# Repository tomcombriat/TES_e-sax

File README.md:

# TES - e-sax

More infos: https://t-e-s.frama.site/en/tesaxophone

The E-sax is an EWI made out of a real sax. It outputs MIDI signals that can be used to generate sounds using a synthesizer for instance the [10k synth](https://github.com/tomcombriat/TES_10-knobs-synth). It is design to provide saxophone players a digital instrument to which they can transition easily. Additionnaly from the "standard" behavior it also have features that are allowed by a digital instrument:

- EWI mode which tries to give a more ergonomic keying (E mode)
- chords (C mode)
- arpegiators (A and R modes)

## What is in this repo?
The [hardware](hardware/) folder contains the kicad project for the PCB used in the e-sax alongside with the Cu and Fab masks. It is single sided in order to make its construction possible for an hobbyist. Note that the isolations and the routes are fairly small (around 200 microns) so you will need to have a fairly optimized setup to be able to make this PCB correctly.

The [software](software/) folder contains the embedded program that is embedded in the chip. Note that it will need some configurations for any particular saxophone.

The main MCU is a cheap BluePill STM32, programmed using the [Arduino STM32 library](https://github.com/stm32duino/Arduino_Core_STM32) and a FTDI.

## Making
This gives some guidelines in order to allow people to make such an E-sax themselves. It precludes that the PCB is already printed and drilled.

Note: no 3D parts are included in this repo for now. Except for the beak, every part usually need to be redesigned for a different saxophone. Do not hesitate to contact me on that.

### Bill of Materials 

- 24 resistors 1-10k, noted R on the PCB
- 1 resistor 33
- 2 resistors 22k (optionnal)
- 1 resistor 10
- 1 BluePill
- 1 FTDI chip to program the BluePill
- 3 74HC165 Parallel-to-Serial shift registers
- enough header
- 1 SSD1306 Oled screen (*I2C*)
- 1 MPX5010 differential pressure sensor
- 1 joystick with a click
- a good amount of flexible thin wire (around 26 AWG, silicon cover)
- Dupond cables
- a good amount of copper tape
- 1 3-AA battery holder
- 1 MIDI female to solder
- 1 switch (non-momentary)
- 2 pairs (male and female) of JST connectors 3 pins
- 1 pair of JST connectors 5 pins
- 10 magnets (10x4x2mm^3) (optionnal)

### Wiring the saxophone

The controller needs to know what keys are pressed at any given time in order to be able to generate the correct MidiNote for a synthesizer. In order for the behavior to be as close as possible to a real saxophone, the sensors are positionned on the pads and not on the keys: if a key closing a pad is not pressed enough to close the pad the controller will consider it "open" just like it would be for a real saxophone. All the wires for the pads are going through the sax body.

The saxophone is a complex instrument and not every pad can be dismounted "alone": it is usual that some of them need other to be removed first in order to be dismounted.

#### Dismounting
This is why it is usually easier to dismount all the keys first and wire them on remounting.
Note: take some notes about which keys did you dismounted first: as the order matters they will need to be remounted in the _reverse order_. My personnal way of doing it is to write on every part a number and a letter (the latter only if this is a pad): the number denotes the order of dismounting (first dismounted part will be labelled "1", second "2"…) and the letter denotes the hole the pad is covering. I also write the same letter next to, or in, the hole which is covered by the pad. This way, upon remounting, one can start by the part with highest number, spot its hole (if any) and remount it.

#### Wiring the pads

The pads can be wired upon remounting. All pads need to be wired except the one which is just above the left hand forefinger which is not independant from the pad located under the left hand forefinger.

The sensor is composed of a thin copper layer glued to the pad and wire to the PCB. Using a push-up resistor, and by placing the whole sax body at GND the pad will behave as a switch:

- closed, the potential of the copper part will be at GND as it is in contact with the body
- open, the potential will be at 3.3V, thanks to a push-up resistor.

The copper tape needs to be glued to the pad:

- cut a piece of copper tape that matches more or less the dimension of the pad. The exact size of this piece is not critical but:
  - it need to cover some of the parts of the pad which are in contact with the body when closed. If possible at two different locations meaning that the length of this copper part should be at least be equal to the diameter of the hole covered by the pad.
  - it should not be too long either in order not to touch the metallic part of the key.
- apply a thin layer of neopren glue on the **tape** side of the copper, it should cover it all. Beware not to put some glue on the "clear" part of the copper
- apply a thin layer of neopren on the pad, it should match the dimensions of the piece of copper.
- wait from 10 to 15 minutes
- apply the copper, glue side of the tape facing the glue side of the pad, it should stick immediatly so the first attempt should be well positionned.
- using a soldering iron, add some solder at **the middle of the pad**, it should not touch the part where the pad touches the body.
- soldier a flexible wire long enough to go from the corresponding hole to the bell plus 5cm to it.
- put the wire in the hole and make it go to the bell throught the body (this can be hard for some keys) and tape it to the bell.
- remount the key on its hole.
- if done correctly, the key should action seemlessly and feel as natural as before.
- start again for all the other keys.

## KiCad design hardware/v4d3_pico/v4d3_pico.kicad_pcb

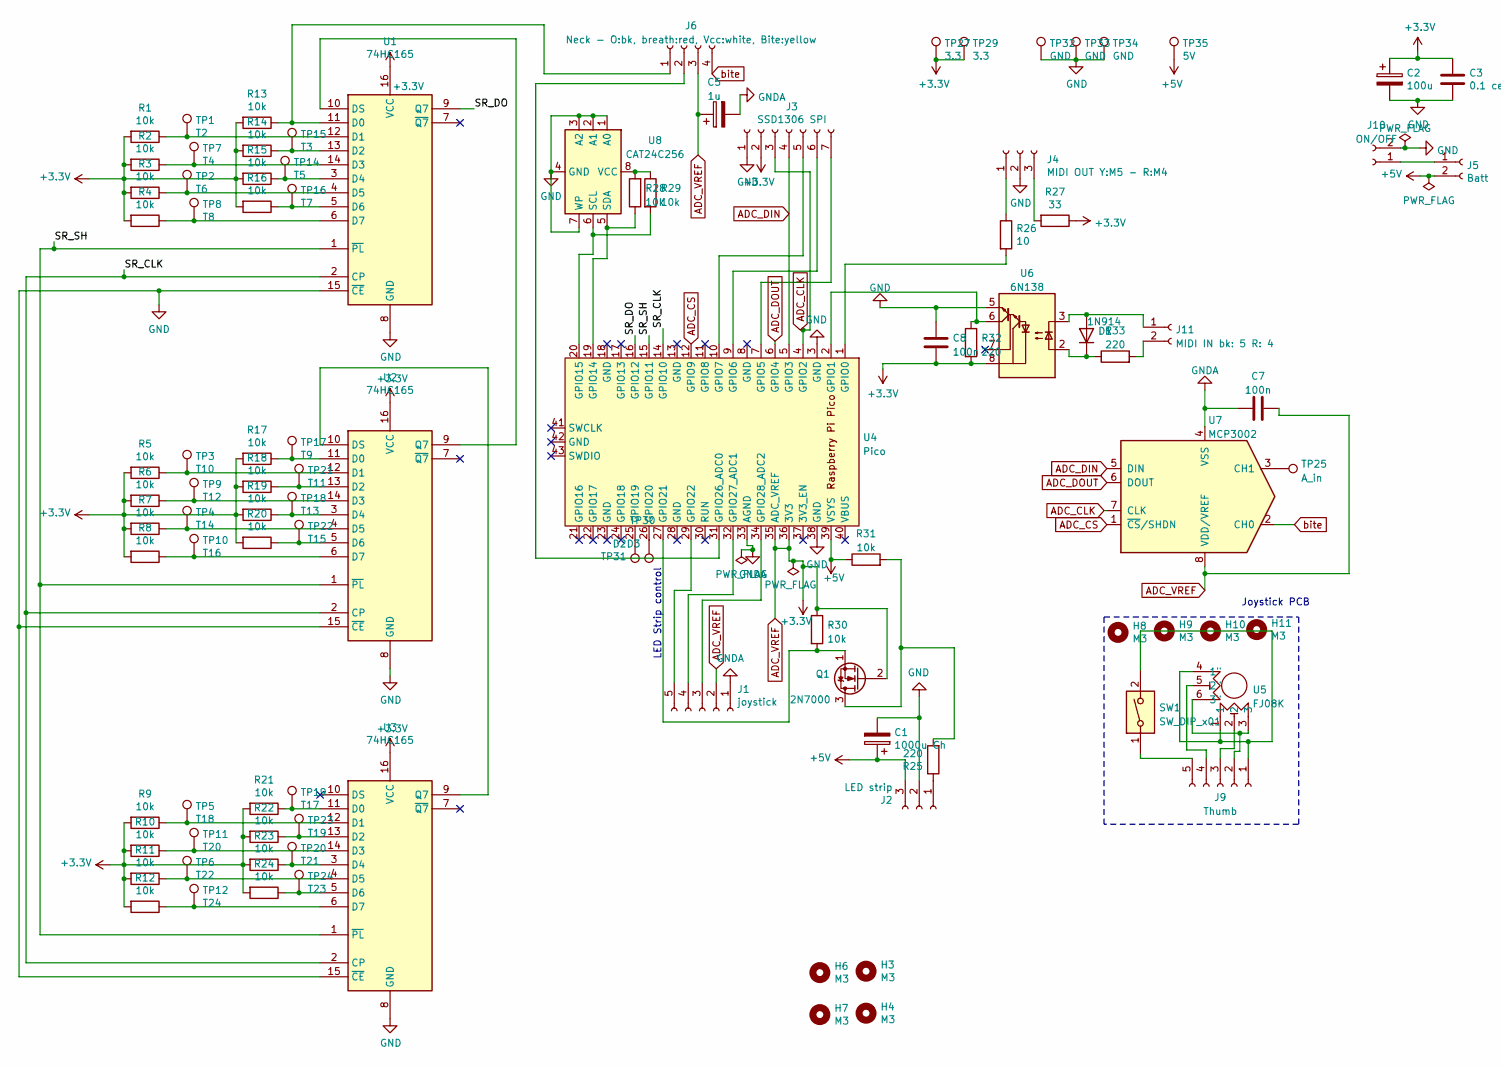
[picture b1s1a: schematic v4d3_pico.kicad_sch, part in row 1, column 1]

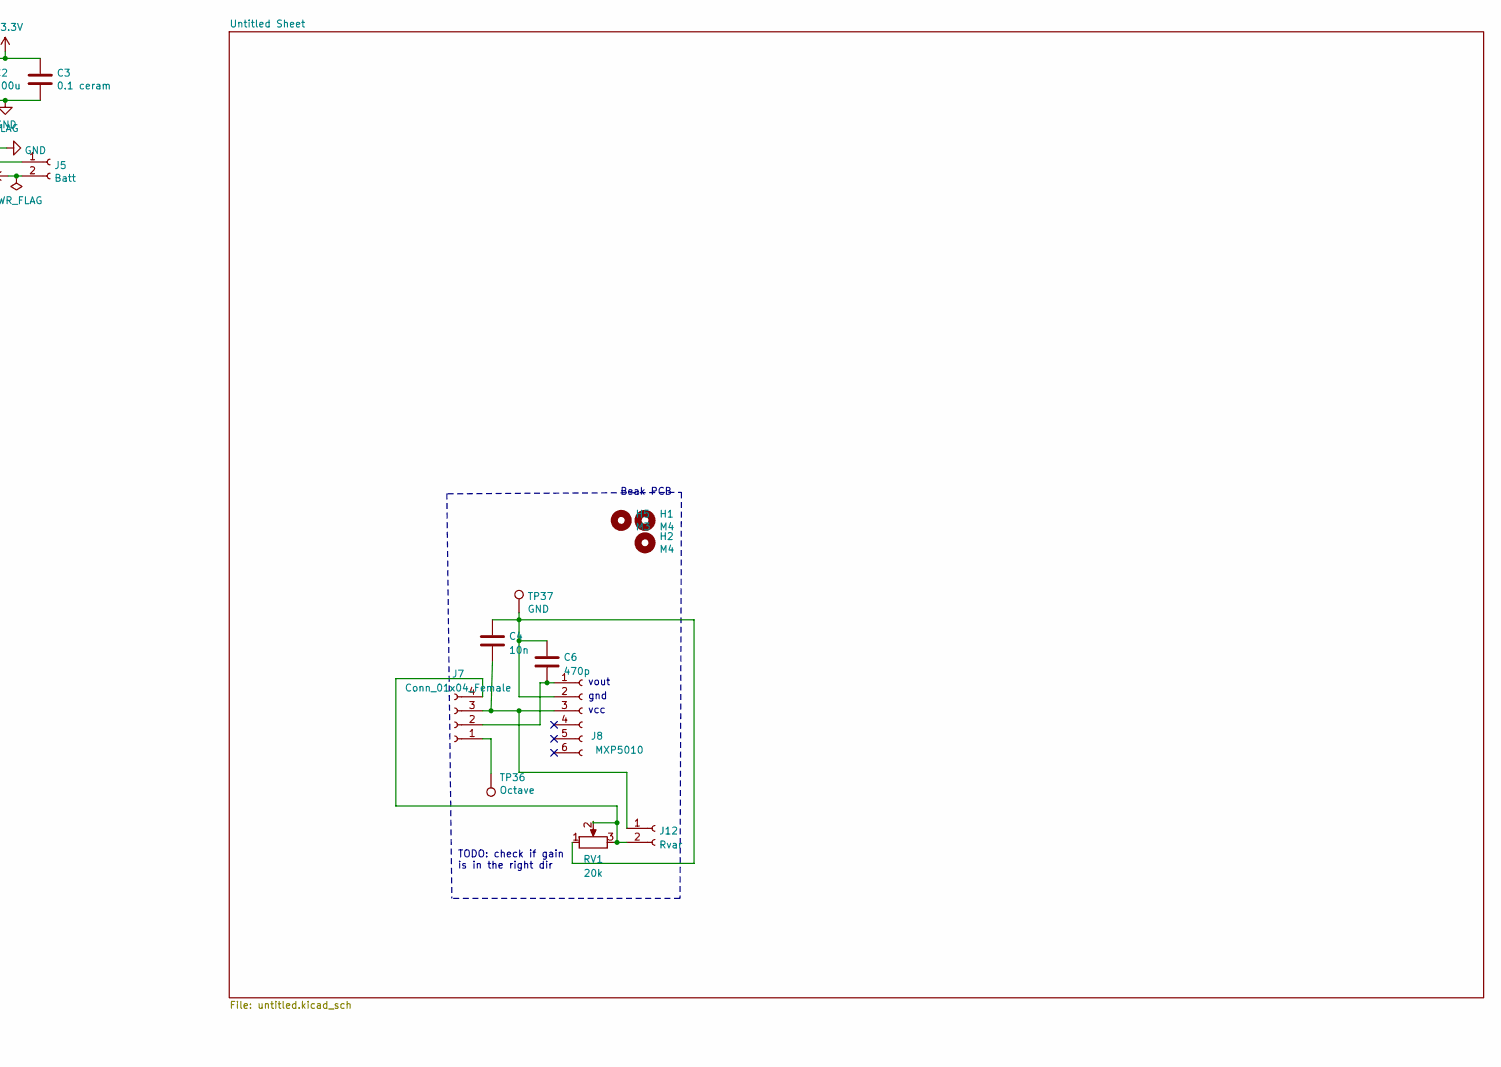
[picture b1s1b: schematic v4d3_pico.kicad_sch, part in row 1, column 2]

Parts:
C1: 1000u Ch; CP_Radial_D8.0mm_P3.50mm
C2: 100u; CP_Radial_D5.0mm_P2.50mm
C3: 0.1 ceram; C_Disc_D3.4mm_W2.1mm_P2.50mm
C4: 10n; C_Disc_D3.4mm_W2.1mm_P2.50mm
C5: 1u; CP_Radial_D4.0mm_P2.00mm
C6: 470p; C_Disc_D3.4mm_W2.1mm_P2.50mm
C7, C8: 100n; C_Axial_L3.8mm_D2.6mm_P7.50mm_Horizontal
D1: 1N914; D_DO-34_SOD68_P7.62mm_Horizontal
H1, H2: M4; MountingHole_4.3mm_M4
H3, H4, H5, H6, H7, H8, H9, H10, H11: M3; MountingHole_3.2mm_M3_ISO14580
J1: joystick; JST_PH_B5B-PH-K_1x05_P2.00mm_Vertical
J2: LED strip; JST_PH_S3B-PH-K_1x03_P2.00mm_Horizontal
J3: SSD1306 SPI; JST_PH_B7B-PH-K_1x07_P2.00mm_Vertical
J4: MIDI OUT Y:M5 - R:M4; JST_PH_S3B-PH-K_1x03_P2.00mm_Horizontal
J5: Batt; JST_XH_S2B-XH-A_1x02_P2.50mm_Horizontal
J6: Neck - O:bk, breath:red, Vcc:white, Bite:yellow; JST_PH_B4B-PH-K_1x04_P2.00mm_Vertical
J7: Conn_01x04_Female; JST_PH_B4B-PH-K_1x04_P2.00mm_Vertical
J8: MXP5010; PinSocket_1x06_P2.54mm_Vertical
J9: Thumb; JST_PH_S5B-PH-K_1x05_P2.00mm_Horizontal
J10: ON/OFF; JST_XH_S2B-XH-A_1x02_P2.50mm_Horizontal
J11: MIDI IN bk: 5 R: 4; JST_XH_S2B-XH-A_1x02_P2.50mm_Horizontal
J12: Rvar; JST_XH_B2B-XH-A_1x02_P2.50mm_Vertical
Q1: 2N7000; TO-92L_HandSolder
R1, R2, R3, R4, R5, R6, R7, R8, R9, R10, R11, R12, R13, R14, R15, R16, R17, R18, R19, R20, R21, R22, R23, R24, R28, R29, R30: 10k; R_1206_3216Metric_Pad1.30x1.75mm_HandSolder
R25, R32, R33: 220; R_Axial_DIN0207_L6.3mm_D2.5mm_P7.62mm_Horizontal
R26: 10; R_Axial_DIN0207_L6.3mm_D2.5mm_P7.62mm_Horizontal
R27: 33; R_Axial_DIN0207_L6.3mm_D2.5mm_P7.62mm_Horizontal
R31: 10k; R_Axial_DIN0207_L6.3mm_D2.5mm_P7.62mm_Horizontal
RV1: 20k; Potentiometer_Runtron_RM-065_Vertical
SW1: SW_DIP_x01; Multi_switch
TP1: T2; TestPoint_THTPad_2.5x2.5mm_Drill1.2mm
TP2: T6; TestPoint_THTPad_2.5x2.5mm_Drill1.2mm
TP3: T10; TestPoint_THTPad_2.5x2.5mm_Drill1.2mm
TP4: T14; TestPoint_THTPad_2.5x2.5mm_Drill1.2mm
TP5: T18; TestPoint_THTPad_2.5x2.5mm_Drill1.2mm
TP6: T22; TestPoint_THTPad_2.5x2.5mm_Drill1.2mm
TP7: T4; TestPoint_THTPad_2.5x2.5mm_Drill1.2mm
TP8: T8; TestPoint_THTPad_2.5x2.5mm_Drill1.2mm
TP9: T12; TestPoint_THTPad_2.5x2.5mm_Drill1.2mm
TP10: T16; TestPoint_THTPad_2.5x2.5mm_Drill1.2mm
TP11: T20; TestPoint_THTPad_2.5x2.5mm_Drill1.2mm
TP12: T24; TestPoint_THTPad_2.5x2.5mm_Drill1.2mm
TP14: T5; TestPoint_THTPad_2.5x2.5mm_Drill1.2mm
TP15: T3; TestPoint_THTPad_2.5x2.5mm_Drill1.2mm
TP16: T7; TestPoint_THTPad_2.5x2.5mm_Drill1.2mm
TP17: T9; TestPoint_THTPad_2.5x2.5mm_Drill1.2mm
TP18: T13; TestPoint_THTPad_2.5x2.5mm_Drill1.2mm
TP19: T17; TestPoint_THTPad_2.5x2.5mm_Drill1.2mm
TP20: T21; TestPoint_THTPad_2.5x2.5mm_Drill1.2mm
TP21: T11; TestPoint_THTPad_2.5x2.5mm_Drill1.2mm
TP22: T15; TestPoint_THTPad_2.5x2.5mm_Drill1.2mm
TP23: T19; TestPoint_THTPad_2.5x2.5mm_Drill1.2mm
TP24: T23; TestPoint_THTPad_2.5x2.5mm_Drill1.2mm
TP25: A_in; TestPoint_THTPad_2.5x2.5mm_Drill1.2mm
TP27, TP29: 3.3; TestPoint_THTPad_2.5x2.5mm_Drill1.2mm
TP30: D3; TestPoint_THTPad_2.5x2.5mm_Drill1.2mm
TP31: D2; TestPoint_THTPad_2.5x2.5mm_Drill1.2mm
TP32, TP33, TP34, TP37: GND; TestPoint_THTPad_2.5x2.5mm_Drill1.2mm
TP35: 5V; TestPoint_THTPad_2.5x2.5mm_Drill1.2mm
TP36: Octave; TestPoint_THTPad_2.5x2.5mm_Drill1.2mm
U1, U2, U3: 74HC165; SOIC-16_3.9x9.9mm_P1.27mm
U4: Pico; RPi_Pico_TH
U5: FJ08K
U6: 6N138; DIP-8_W7.62mm_Socket
U7: MCP3002; DIP-8_W7.62mm
U8: CAT24C256; DIP-8_W7.62mm_Socket

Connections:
+5V: C1.1, J2.3, J5.2, R31.1, TP35.1, U4.39 (VSYS)
/SR_CLK: U1.2 (CP), U2.2 (CP), U3.2 (CP), U4.14 (GPIO10)
/SR_DO: U1.9 (Q7), U4.16 (GPIO12)
/SR_SH: U1.1 (~PL), U2.1 (~PL), U3.1 (~PL), U4.15 (GPIO11)
ADC_CLK: J3.3, U4.4 (GPIO2), U7.7 (CLK)
ADC_CS: U4.12 (GPIO9), U7.1 (~CS/SHDN)
ADC_DIN: J3.4, U4.5 (GPIO3), U7.5 (DIN)
ADC_DOUT: U4.6 (GPIO4), U7.6 (DOUT)
ADC_VREF: C2.1, C3.1, C5.1, C7.2, C8.2, J1.2, J3.2, J6.3, Q1.2 (G), R1.2, R2.2, R3.2, R4.2, R5.2, R6.2, R7.2, R8.2, R9.2, R10.2, R11.2, R12.2, R13.2, R14.2, R15.2, R16.2, R17.2, R18.2, R19.2, R20.2, R21.2, R22.2, R23.2, R24.2, R27.1, R30.1, R32.2, TP27.1, TP29.1, U1.16 (VCC), U2.16 (VCC), U3.16 (VCC), U4.35 (ADC_VREF), U4.36 (3V3), U6.8 (VCC), U7.8 (VDD/VREF)
GND: C1.2, C2.2, C3.2, C8.1, J2.2, J3.1, J4.2, J10.2, TP32.1, TP33.1, TP34.1, U1.8 (GND), U1.15 (~CE), U2.8 (GND), U2.15 (~CE), U3.8 (GND), U3.15 (~CE), U4.3 (GND), U4.38 (GND), U6.5 (GND), U8.1 (A0), U8.2 (A1), U8.3 (A2), U8.4 (GND), U8.7 (WP)
GNDA: C5.2, C7.1, J1.1, U4.33 (AGND), U7.4 (VSS)
unnamed: D1.2 (A), J11.1, U6.3 (C2)
unnamed: D1.1 (K), R33.1, U6.2 (C1)
unnamed: J1.3, U4.34 (GPIO28_ADC2)
unnamed: J1.4, U4.32 (GPIO27_ADC1)
unnamed: J1.5, U4.29 (GPIO22)
unnamed: J2.1, R25.1
unnamed: J3.5, U4.10 (GPIO7)
unnamed: J3.6, U4.9 (GPIO6)
unnamed: J3.7, U4.7 (GPIO5)
unnamed: J4.1, R26.1
unnamed: J4.3, R27.2
unnamed: J6.1, R13.1, U1.11 (D0)
unnamed: J6.2, U4.31 (GPIO26_ADC0)
unnamed: J7.1, TP36.1
unnamed: C6.2, J7.2, J8.1
unnamed: C4.1, C6.1, J8.2, RV1.1, TP37.1
unnamed: J9.1, SW1.2, U5.1, U5.4 (1")
unnamed: J9.2, U5.3, U5.6 (3")
unnamed: J9.3, U5.2
unnamed: J9.4, U5.5 (2")
unnamed: J9.5, SW1.1
unnamed: J5.1, J10.1
unnamed: J11.2, R33.2
unnamed: C4.2, J7.3, J8.3, J12.1
unnamed: J7.4, J12.2, RV1.2, RV1.3
unnamed: Q1.3 (D), R25.2, R31.2
unnamed: Q1.1 (S), R30.2, U4.27 (GPIO21)
unnamed: R1.1, TP1.1, U1.12 (D1)
unnamed: R14.1, TP15.1, U1.13 (D2)
unnamed: R2.1, TP7.1, U1.14 (D3)
unnamed: R15.1, TP14.1, U1.3 (D4)
unnamed: R3.1, TP2.1, U1.4 (D5)
unnamed: R16.1, TP16.1, U1.5 (D6)
unnamed: R4.1, TP8.1, U1.6 (D7)
unnamed: U1.10 (DS), U2.9 (Q7)
unnamed: R17.1, TP17.1, U2.11 (D0)
unnamed: R5.1, TP3.1, U2.12 (D1)
unnamed: R18.1, TP21.1, U2.13 (D2)
unnamed: R6.1, TP9.1, U2.14 (D3)
unnamed: R19.1, TP18.1, U2.3 (D4)
unnamed: R7.1, TP4.1, U2.4 (D5)
unnamed: R20.1, TP22.1, U2.5 (D6)
unnamed: R8.1, TP10.1, U2.6 (D7)
unnamed: U2.10 (DS), U3.9 (Q7)
unnamed: R21.1, TP19.1, U3.11 (D0)
unnamed: R9.1, TP5.1, U3.12 (D1)
unnamed: R22.1, TP23.1, U3.13 (D2)
unnamed: R10.1, TP11.1, U3.14 (D3)
unnamed: R23.1, TP20.1, U3.3 (D4)
unnamed: R11.1, TP6.1, U3.4 (D5)
unnamed: R24.1, TP24.1, U3.5 (D6)
unnamed: R12.1, TP12.1, U3.6 (D7)
unnamed: R26.2, U4.1 (GPIO0)
unnamed: R32.1, U4.2 (GPIO1), U6.6 (VO2)
unnamed: R28.1, U4.19 (GPIO14), U8.5 (SDA)
unnamed: R29.2, U4.20 (GPIO15), U8.6 (SCL)
unnamed: TP31.1, U4.25 (GPIO19)
unnamed: TP30.1, U4.26 (GPIO20)
unnamed: TP25.1, U7.3 (CH1)
unnamed: R28.2, R29.1, U8.8 (VCC)
bite: J6.4, U7.2 (CH0)

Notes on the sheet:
vcc
TODO: check if gain is in the right dir
gnd
Joystick PCB
vout
Beak PCB
LED Strip control

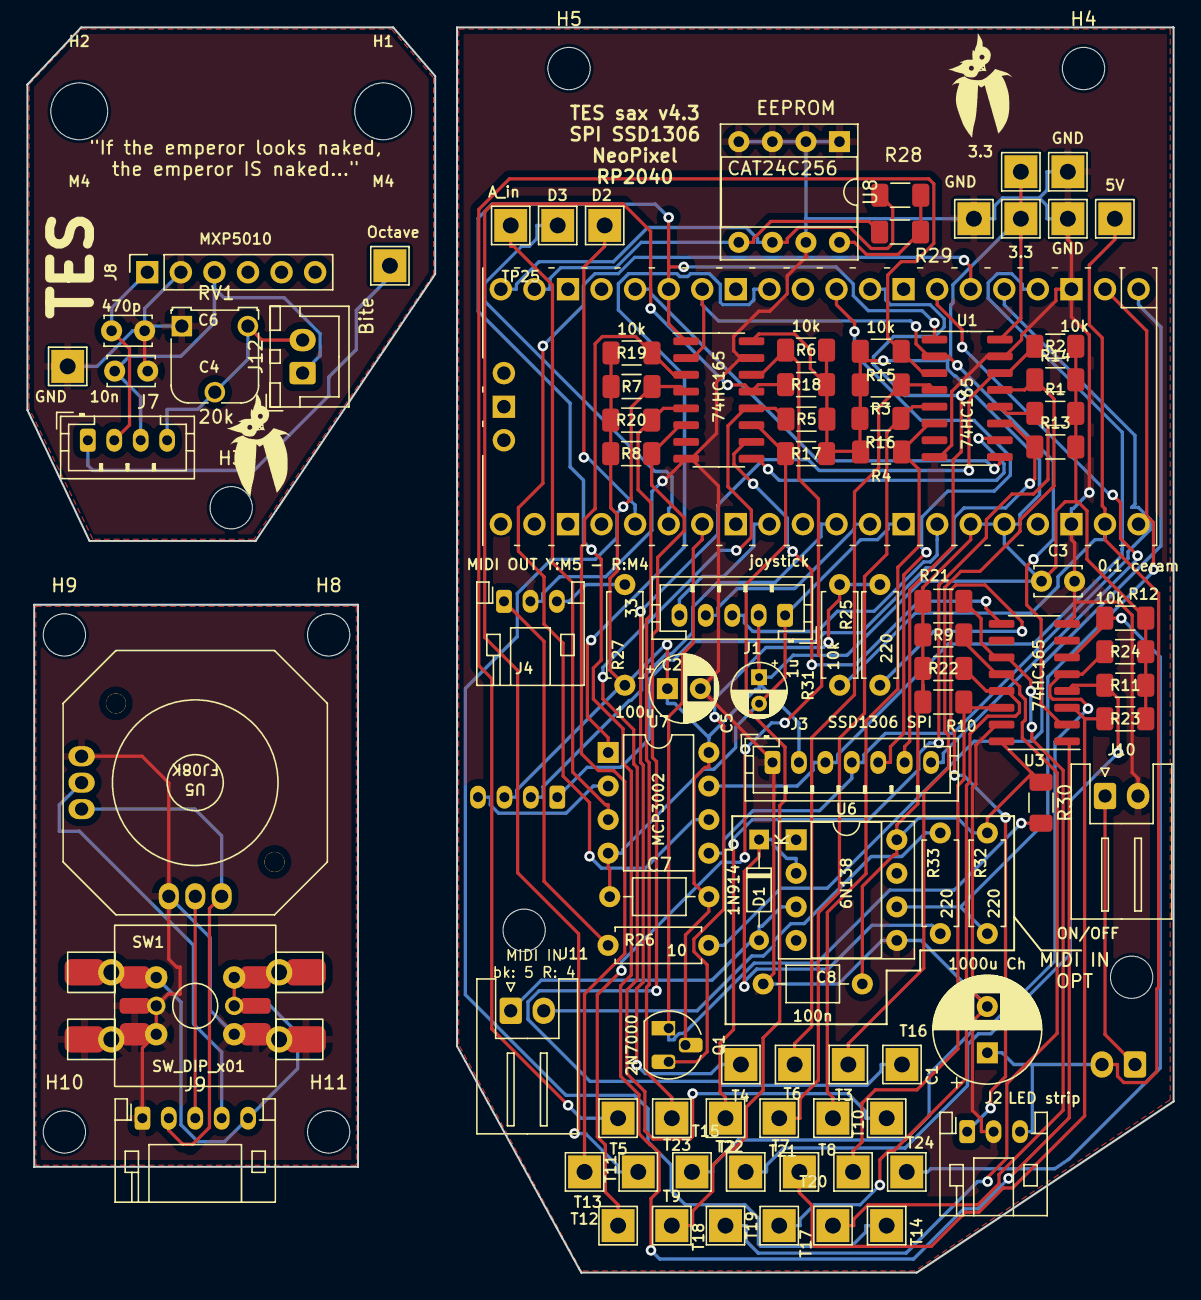
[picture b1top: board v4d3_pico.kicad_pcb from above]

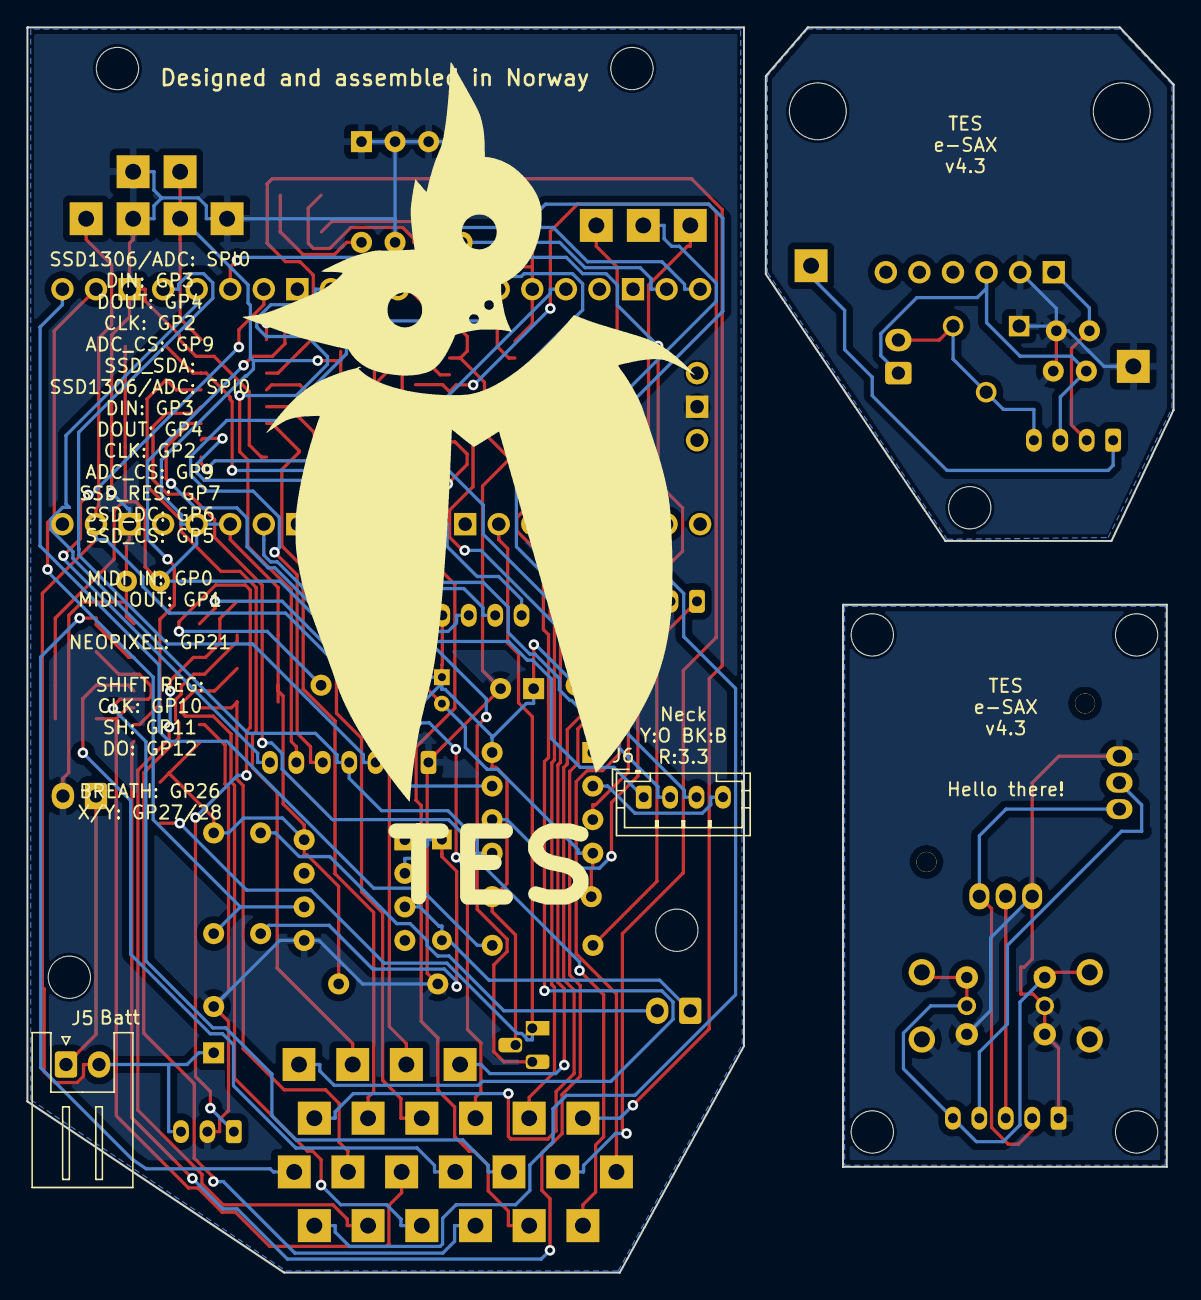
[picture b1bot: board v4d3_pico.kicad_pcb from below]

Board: 2 copper layers, 86.7 x 94.2 mm, 113 parts (3 on the bottom side), 72 nets.

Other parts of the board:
owl_beak: LOGO; owl_7x10
owl_big_pcb: LOGO; owl_F_50x70
owl_small_pcb: LOGO; owl_7x10

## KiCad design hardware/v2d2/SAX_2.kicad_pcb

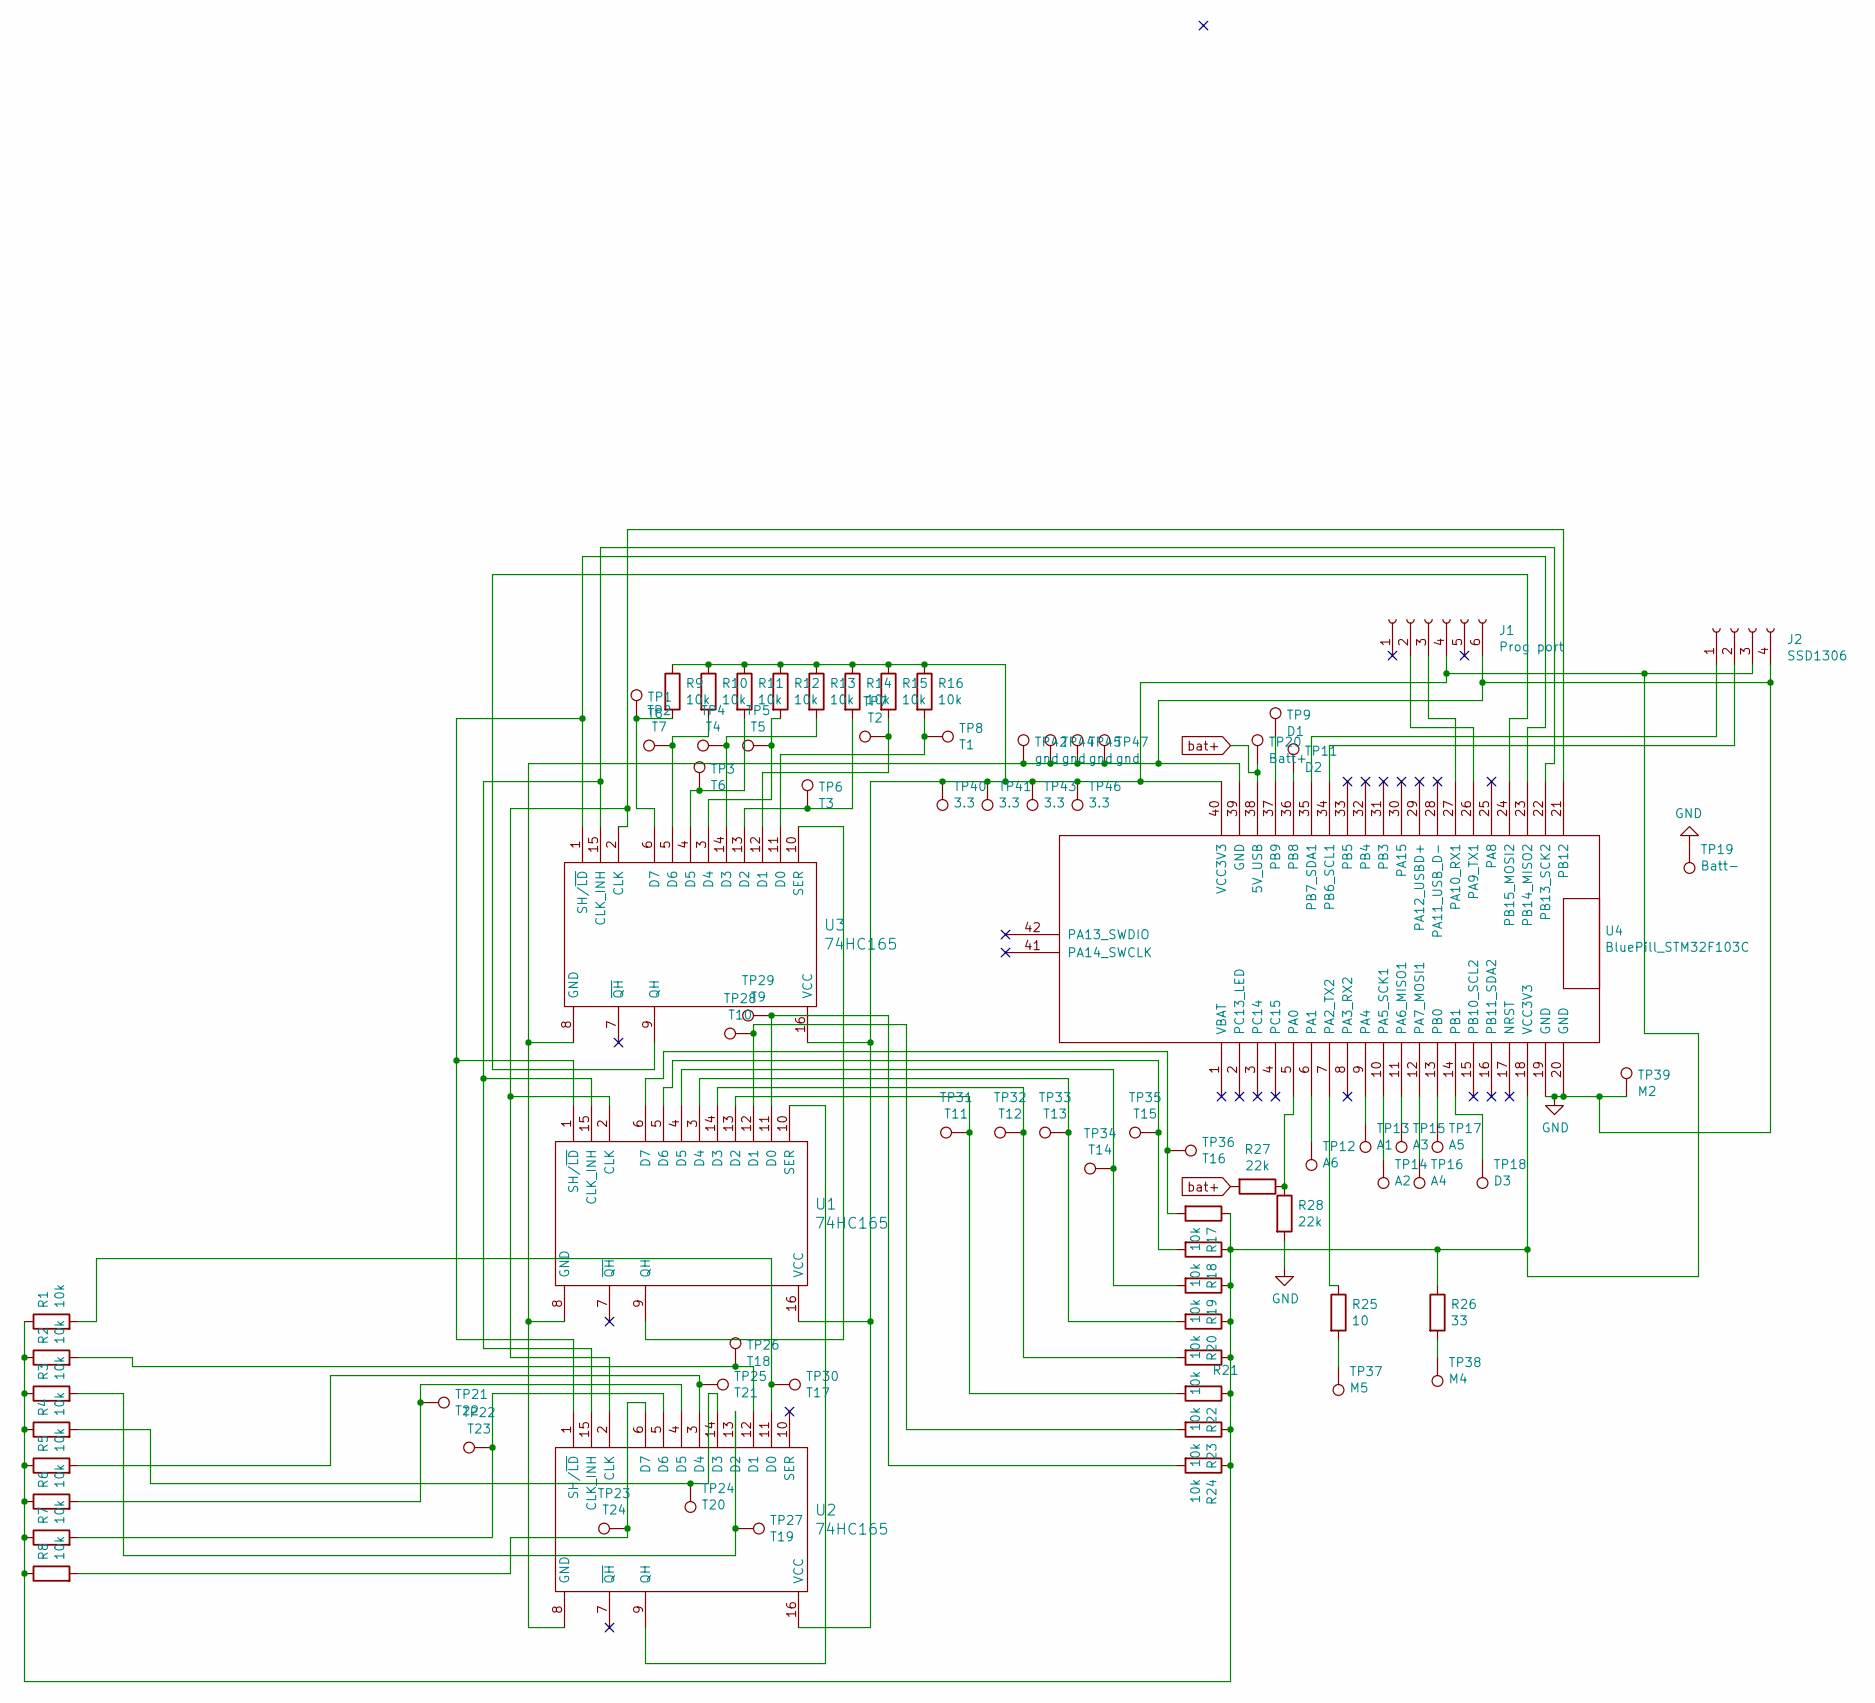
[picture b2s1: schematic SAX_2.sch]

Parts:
J1: Prog port; PinSocket_1x06_P2.54mm_Vertical
J2: SSD1306; PinSocket_1x04_P2.54mm_Vertical
R1, R2, R3, R4, R5, R6, R7, R8, R9, R10, R11, R12, R13, R14, R15, R16, R17, R18, R19, R20, R21, R22, R23, R24: 10k; R_Axial_DIN0207_L6.3mm_D2.5mm_P7.62mm_Horizontal
R25: 10; R_Axial_DIN0207_L6.3mm_D2.5mm_P7.62mm_Horizontal
R26: 33; R_Axial_DIN0207_L6.3mm_D2.5mm_P7.62mm_Horizontal
R27, R28: 22k; R_Axial_DIN0207_L6.3mm_D2.5mm_P7.62mm_Horizontal
TP1: T8; TestPoint_THTPad_D2.0mm_Drill1.0mm
TP2: T7; TestPoint_THTPad_D2.0mm_Drill1.0mm
TP3: T6; TestPoint_THTPad_D2.0mm_Drill1.0mm
TP4: T4; TestPoint_THTPad_D2.0mm_Drill1.0mm
TP5: T5; TestPoint_THTPad_D2.0mm_Drill1.0mm
TP6: T3; TestPoint_THTPad_D2.0mm_Drill1.0mm
TP7: T2; TestPoint_THTPad_D2.0mm_Drill1.0mm
TP8: T1; TestPoint_THTPad_D2.0mm_Drill1.0mm
TP9: D1; TestPoint_THTPad_D2.0mm_Drill1.0mm
TP11: D2; TestPoint_THTPad_D2.0mm_Drill1.0mm
TP12: A6; TestPoint_THTPad_D2.0mm_Drill1.0mm
TP13: A1; TestPoint_THTPad_D2.0mm_Drill1.0mm
TP14: A2; TestPoint_THTPad_D2.0mm_Drill1.0mm
TP15: A3; TestPoint_THTPad_D2.0mm_Drill1.0mm
TP16: A4; TestPoint_THTPad_D2.0mm_Drill1.0mm
TP17: A5; TestPoint_THTPad_D2.0mm_Drill1.0mm
TP18: D3; TestPoint_THTPad_D2.0mm_Drill1.0mm
TP19: Batt-; TestPoint_THTPad_D2.0mm_Drill1.0mm
TP20: Batt+; TestPoint_THTPad_D2.0mm_Drill1.0mm
TP21: T22; TestPoint_THTPad_D2.0mm_Drill1.0mm
TP22: T23; TestPoint_THTPad_D2.0mm_Drill1.0mm
TP23: T24; TestPoint_THTPad_D2.0mm_Drill1.0mm
TP24: T20; TestPoint_THTPad_D2.0mm_Drill1.0mm
TP25: T21; TestPoint_THTPad_D2.0mm_Drill1.0mm
TP26: T18; TestPoint_THTPad_D2.0mm_Drill1.0mm
TP27: T19; TestPoint_THTPad_D2.0mm_Drill1.0mm
TP28: T10; TestPoint_THTPad_D2.0mm_Drill1.0mm
TP29: T9; TestPoint_THTPad_D2.0mm_Drill1.0mm
TP30: T17; TestPoint_THTPad_D2.0mm_Drill1.0mm
TP31: T11; TestPoint_THTPad_D2.0mm_Drill1.0mm
TP32: T12; TestPoint_THTPad_D2.0mm_Drill1.0mm
TP33: T13; TestPoint_THTPad_D2.0mm_Drill1.0mm
TP34: T14; TestPoint_THTPad_D2.0mm_Drill1.0mm
TP35: T15; TestPoint_THTPad_D2.0mm_Drill1.0mm
TP36: T16; TestPoint_THTPad_D2.0mm_Drill1.0mm
TP37: M5; TestPoint_THTPad_D2.0mm_Drill1.0mm
TP38: M4; TestPoint_THTPad_D2.0mm_Drill1.0mm
TP39: M2; TestPoint_THTPad_D2.0mm_Drill1.0mm
TP40, TP41, TP43, TP46: 3.3; TestPoint_THTPad_D2.0mm_Drill1.0mm
TP42, TP44, TP45, TP47: gnd; TestPoint_THTPad_D2.0mm_Drill1.0mm
U1, U2, U3: 74HC165; DIP-16_W7.62mm
U4: BluePill_STM32F103C

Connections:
GND: J1.6, J2.4, R28.2, TP19.1, TP39.1, TP42.1, TP44.1, TP45.1, TP47.1, U1.8 (GND), U2.8 (GND), U3.8 (GND), U4.19 (GND), U4.20 (GND), U4.39 (GND)
unnamed: J1.2, U4.26 (PA9_TX1)
unnamed: J1.3, U4.27 (PA10_RX1)
unnamed: J1.4, J2.3, R1.1, R2.1, R3.1, R4.1, R5.1, R6.1, R7.1, R8.1, R9.1, R10.1, R11.1, R12.1, R13.1, R14.1, R15.1, R16.1, R17.1, R18.1, R19.1, R20.1, R21.1, R22.1, R23.1, R24.1, R26.1, TP40.1, TP41.1, TP43.1, TP46.1, U1.16 (VCC), U2.16 (VCC), U3.16 (VCC), U4.18 (VCC3V3), U4.40 (VCC3V3)
unnamed: J2.1, U4.35 (PB7_SDA1)
unnamed: J2.2, U4.34 (PB6_SCL1)
unnamed: R1.2, TP30.1, U2.11 (D0)
unnamed: R2.2, TP26.1, U2.12 (D1)
unnamed: R3.2, TP27.1, U2.13 (D2)
unnamed: R4.2, TP24.1, U2.14 (D3)
unnamed: R5.2, TP25.1, U2.3 (D4)
unnamed: R6.2, TP21.1, U2.4 (D5)
unnamed: R7.2, TP22.1, U2.5 (D6)
unnamed: R8.2, TP23.1, U2.6 (D7)
unnamed: R9.2, TP1.1, U3.6 (D7)
unnamed: R10.2, TP2.1, U3.5 (D6)
unnamed: R11.2, TP3.1, U3.4 (D5)
unnamed: R12.2, TP5.1, U3.3 (D4)
unnamed: R13.2, TP4.1, U3.14 (D3)
unnamed: R14.2, TP6.1, U3.13 (D2)
unnamed: R15.2, TP7.1, U3.12 (D1)
unnamed: R16.2, TP8.1, U3.11 (D0)
unnamed: R17.2, TP36.1, U1.6 (D7)
unnamed: R18.2, TP35.1, U1.5 (D6)
unnamed: R19.2, TP34.1, U1.4 (D5)
unnamed: R20.2, TP33.1, U1.3 (D4)
unnamed: R21.2, TP32.1, U1.14 (D3)
unnamed: R22.2, TP31.1, U1.13 (D2)
unnamed: R23.2, TP28.1, U1.12 (D1)
unnamed: R24.2, TP29.1, U1.11 (D0)
unnamed: R25.1, U4.7 (PA2_TX2)
unnamed: R25.2, TP37.1
unnamed: R26.2, TP38.1
unnamed: R27.1, R28.1, U4.5 (PA0)
unnamed: TP9.1, U4.37 (PB9)
unnamed: TP11.1, U4.36 (PB8)
unnamed: TP12.1, U4.6 (PA1)
unnamed: TP13.1, U4.9 (PA4)
unnamed: TP14.1, U4.10 (PA5_SCK1)
unnamed: TP15.1, U4.11 (PA6_MISO1)
unnamed: TP16.1, U4.12 (PA7_MOSI1)
unnamed: TP17.1, U4.13 (PB0)
unnamed: TP18.1, U4.14 (PB1)
unnamed: U1.1 (SH/~LD), U2.1 (SH/~LD), U3.1 (SH/~LD), U4.23 (PB14_MISO2)
unnamed: U1.2 (CLK), U2.2 (CLK), U3.2 (CLK), U4.21 (PB12)
unnamed: U1.9 (QH), U3.10 (SER)
unnamed: U1.10 (SER), U2.9 (QH)
unnamed: U1.15 (CLK_INH), U2.15 (CLK_INH), U3.15 (CLK_INH), U4.22 (PB13_SCK2)
unnamed: U3.9 (QH), U4.24 (PB15_MOSI2)
bat+: R27.2, TP20.1, U4.38 (5V_USB)

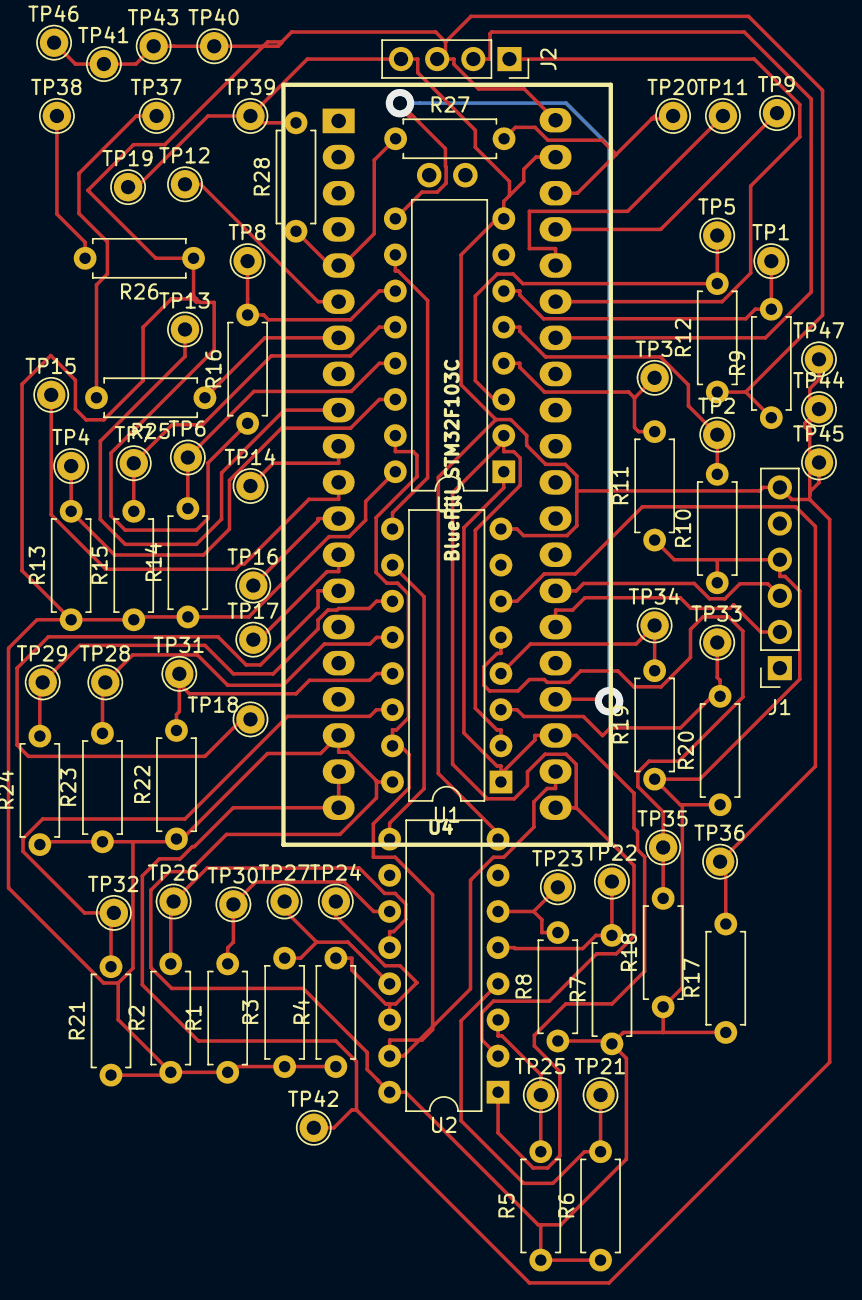
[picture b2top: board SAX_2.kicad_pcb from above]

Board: 2 copper layers, 80 parts (0 on the bottom side), 50 nets.

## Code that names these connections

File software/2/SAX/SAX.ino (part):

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#define PITCHBEND_MIN_TIME 10
#define SCREEN_UPDATE_TIME 20
#define SCREEN_IDLE_WAITING_TIME 400
#define BATT_PIN PA0



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/***************************/
/****** ANALOG INPUTS ******/
/***************************/
analog_input joy_Y(PB0, 0, JOYSTICK_RESPONSE_TIME);
analog_input joy_X(PA7, 0, JOYSTICK_RESPONSE_TIME);
analog_input breath(PA1, 0, BREATH_RESPONSE_TIME, 20);


/***************************/
/********* BUTTONS *********/
/***************************/
button joy_SW(PB1, false, JOYSTICK_RESPONSE_TIME);
button octave(-1, true, MODIFIER_RESPONSE_TIME);
button modifier_up(-1, true, MODIFIER_RESPONSE_TIME);
button modifier_mid(-1, true, MODIFIER_RESPONSE_TIME);
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
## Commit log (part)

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2020-02-26 Create LICENSE
2020-02-26 Added hardware o
2020-02-26 Suppressed duplicated files
2020-02-26 Del dup
2020-03-02 Moved into a dir properly nammed for Arduino
2020-03-02 Added three arpegiators
2020-03-02 Add comments, decreased minimum available tempo
2020-03-02 Added few comments
2020-03-02 Removed unneeded functions
2020-03-02 Delta mode by default
2020-03-03 Added one arp
2020-04-14 Corrected tap tempo, completed chord_mode
2020-04-16 Added chords and one arp. Corrected wrong logic for both
2020-04-16 Removed serial
2020-04-16 Small optimization
2020-04-18 Added a time limiter for MIDI NOTE ON/OFF to avoid jamming
2020-04-18 Corrected timing issue with CHORD: up, mid and down now have null response time
2020-04-19 Corrected wrong logic in button class
2020-04-19 Corrected a wrong pointer on ARP, was messing random stuff. Optimized tap_tempo in the mean time
2020-04-26 Comment on future small optimization
2020-05-01 Added possibility to change PB range
2020-05-02 Menu is now displaying the notes when choosing an Arp or a Chord
2020-05-02 Arp performance test
2020-05-13 New branch to test another arp
2020-05-13 Test
2020-05-18 Added long names to arp
2020-05-18 Added long names for chords
2020-05-18 Added crazy tempo
2020-05-18 Arp now 25x faster
2020-05-18 Removed unneccessary comments
2020-05-19 Fixed chords, broken by previous commits
2020-05-19 Wrong long chords names
2020-05-21 Added 7th, sus2 and sus4 chord. Changed an Arp
2020-05-21 Changed name of one arp
2020-05-21 Added two chords
2020-05-21 Added chords
2020-05-28 Fixed arpegio, added random arpegiator
2020-05-30 Added alternate fingerings, improved random arp
2020-05-31 Sending chords notes on different midi channel Menu not moving when trying to escape
2020-05-31 Added an arp, enable possibility to have a constant vel (qsynth) and to change breathCC (qsynth)
2020-06-05 small update
2020-06-05 "Started implemented pure sax mode
2020-06-05 Added and implemented Normal mode. Old normal mode is now EWI mode. Corrected a pad, which changed a few fingerings
2020-07-06 Corrected small bug for interaction between chords and octaves (to be tested)
2020-08-23 Added v2.1, allowing to measure battery pourcentage
2020-08-30 Cleaned Pcb, added a comment to test in code
2020-09-01 Added threshold in NoteOn, to avoid glitches between 0 and 1 volume breath values
2020-09-01 Small corrections
2020-09-29 Added midi modifier to SAX mod
2020-10-03 Extra folder for sax SN2
2020-10-03 beginned adapting the code
2020-11-15 Adapted code for inverted joysticks
2020-11-15 Configured correct modifyiers
2020-11-15 Set keys for EWI mode
2020-11-15 Breath ok
2020-11-23 Fixed dead pad
2020-11-23 Fixed compil error
2020-11-23 Adjusted breath sensibility
2020-11-24 Fingerings sax2
2020-11-24 Correct A
2020-11-25 Added interruptCapsense prelim
2020-11-26 Removed unsuccessful capsense :/
2020-11-28 Fixed wrong touches. Batt measurement OK
2021-01-16 Added spaces in PCB
2021-01-20 Improved fab layer
2021-01-21 Added license for SSD1306
2021-03-31 Folder for sax num3
2021-03-31 Removed inverted joystick
2021-03-31 Set modifying keys
2021-03-31 Set keys for non-normal mode
2021-03-31 Set normal keying
2021-04-04 Added presets functions
2021-04-04 Added reset function to button
2021-04-04 Corrected recall of presets
2021-04-04 Added presets to menu
2021-04-04 Improved force update, to really force an update
2021-04-04 Minor corrections
2021-04-04 Added getter and setters for biais
2021-04-04 Updated screen for discering change in title
2021-04-04 Added CC biais in presets
2021-04-04 Added PB amp CC to menu list
2021-04-04 Removed debug comments
2021-04-04 Added not vely convincing battery level check
2021-04-05 Added missing keyings
2021-05-03 Added param to presets
2021-05-03 Added shortcut for presets
2021-05-04 New version of stm32 has correct serial numbers...
2021-05-05 Corrected wrong scaling when retreiving presets
2021-05-06 Values of MIDI_CC do not need to be stored in presets
2021-05-16 Added a kicad project
2021-05-16 Changed number of presets, now split in two pages
2021-06-01 Added curved_analog_input class
2021-06-01 Adapted the code to new class, fixed minor issues
2021-06-20 Updated keyings
2021-08-22 Added calibration for the joystick max value
2021-08-22 cleanup
2021-08-22 Removed surplus
2021-08-22 Breath now encoded on 14bits
2021-08-22 MIDI CC for HQ breath correct
2021-08-25 Fixed chords not playing at max vol
2021-08-28 A bit smoother breath by averaging
2021-09-04 Better unbouncing
2021-09-20 Correction of midi_CC delay
2021-09-20 Timing
2021-10-11 Updated notes, raw batt measurement
2021-10-11 Commit before branch
2021-12-10 Added v3 - Fast screen (SPI) and sourceable Teensy based
2021-12-13 Updated PCB with correct JST connectors, optimized PCB
2021-12-14 Updated pcb
2022-02-20 Added v3d1: better footprnts
2022-02-20 Migrated to kicad v6
2022-05-19 Fixed drift in analogInput
2022-05-22 Initial commit of v3d2
2022-05-30 Added comments
2022-05-30 Working PCB, improvments on breath input filtering
2022-07-31 Added possibility to stack chords, now default
2022-08-10 Initial commit for sax 4
2022-09-17 mapping for E/C/A modes
2022-09-17 Small tests on strand
2022-09-18 Note bindings for sax mode
2022-09-18 Presets in EEPROM working
2022-09-18 Added minimal class for LEDstrand
2022-09-18 Included LEDstrand class in main
2022-09-19 Fixed rollback in menu, attempt for strand effect on startup
2022-09-19 Fixed rollback for presets
2022-09-20 Added LED startup sequence
2022-09-20 strand color following the PB also
2022-09-20 Update touches
2022-10-02 Corrected overflow on joystick
2022-10-02 Added one keying
2022-10-02 Added a mode to remove the LED strand action
2022-10-05 Corrected arp stopping and starting for -255 containing ARP, small opti on 14bits breath
2022-11-09 Threshold on breath for more precision
2022-11-09 Merge
2022-11-09 Updated saxN3, low arp now permitted
2022-11-09 very low threshold on breath
2022-11-14 Last in precedence for modifiers
2022-11-14 Added menu entry for overlapping chords or not
2022-11-18 Added better battery estimate and visual clue
2022-11-19 Removed duplicated code for preset range
2022-11-19 Added batterie display to sax3
2022-11-20 Iimproved screen arrangement, added quick preset changer
2022-11-20 Screen updating on identical presets change
2022-11-20 Updataed sax3 to level of 4
2022-11-20 Corrected overflow in sax3
2022-11-20 Corrected keying on sax4
2022-11-21 Added possibility to assign midi channel for chords separetely
2022-11-26 Bound midi CC to release time of arps
2022-11-27 First commit for SAX2b
2022-11-28 Corrected some keyings
2022-11-28 better keying
2022-12-03 Added some fingerings
2023-03-22 Added joystick dead zone to remove small drift on teensy4
2023-10-01 Started V( hardware sax, with Pico platform. Added footprint for joystick
2023-10-02 Added multiswitch footprint and update FJ08K
2023-10-03 Started porting to pico, LED strip and Joystick moved
2023-10-03 Removed unneeded file
2023-10-03 Added switch on PCB for on/off, neck updated
2023-10-04 Wired screen and shift register v4
2023-10-25 Added ADC component for battery check
2023-11-05 Schematic and assign for saxo pico
2023-11-05 Corrected scheme for DRC«
2023-11-05 Moved adc and screen to same bus
2023-11-05 Updated footprints
2023-11-05 Adapted and tested shift registers on SPI1
2023-11-06 Started PCB
2023-11-06 Work on PCB
2023-11-06 Trying to place everythin on pcb...
2023-11-07 Initial routing
2023-11-09 Improved silk
2023-11-09 Check on courtyarb, placing
2023-11-09 Trying to make room
2023-11-11 PCB cured and routed
2023-11-13 Added Gerber
2023-11-29 Correction on v4
2025-03-24 Updated PCB with bite sensor
2025-04-01 v4d2 of eSax. EEPROM, beak pressure. Schema only
2025-04-01 Added missing files
2025-04-02 Routed PCB
2025-04-06 Updated PCB, gerber export
2025-04-08 Updated PCB for v4.2
2025-04-16 Small fix on beak pcb

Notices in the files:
software/2/SAX/SAX.ino:
This code is under GPL3
BSD license, check license.txt for more information
